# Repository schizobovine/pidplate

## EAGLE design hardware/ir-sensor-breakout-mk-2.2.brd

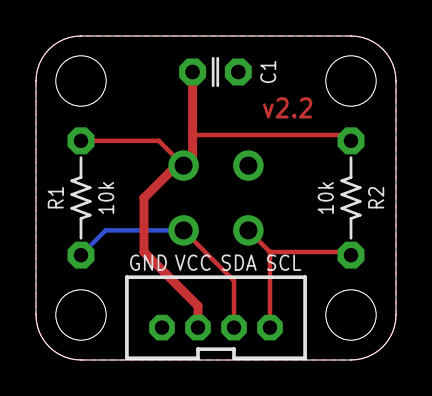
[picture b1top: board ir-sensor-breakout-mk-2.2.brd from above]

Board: 2 copper layers, 20.0 x 18.0 mm, 6 parts (1 on the bottom side), 4 nets.

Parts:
C1: 100nF; C025-024X044
FRAME1: FRAME-LETTERNO_PACKAGE; DUMMY
I2C: M04JST-PTH-VERT; JST-4-PH-VERT-PTH
R1, R2: 10k; RESISTOR-AXIAL-PTH-6.35MM
U1: MLX90614-PTH; TO-39-4

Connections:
GND: C1.2, I2C.1, U1.4
SCL: I2C.4, R2.P$1, U1.1
SDA: I2C.3, R1.P$1, U1.2
VCC: C1.1, I2C.2, R1.P$2, R2.P$2, U1.3

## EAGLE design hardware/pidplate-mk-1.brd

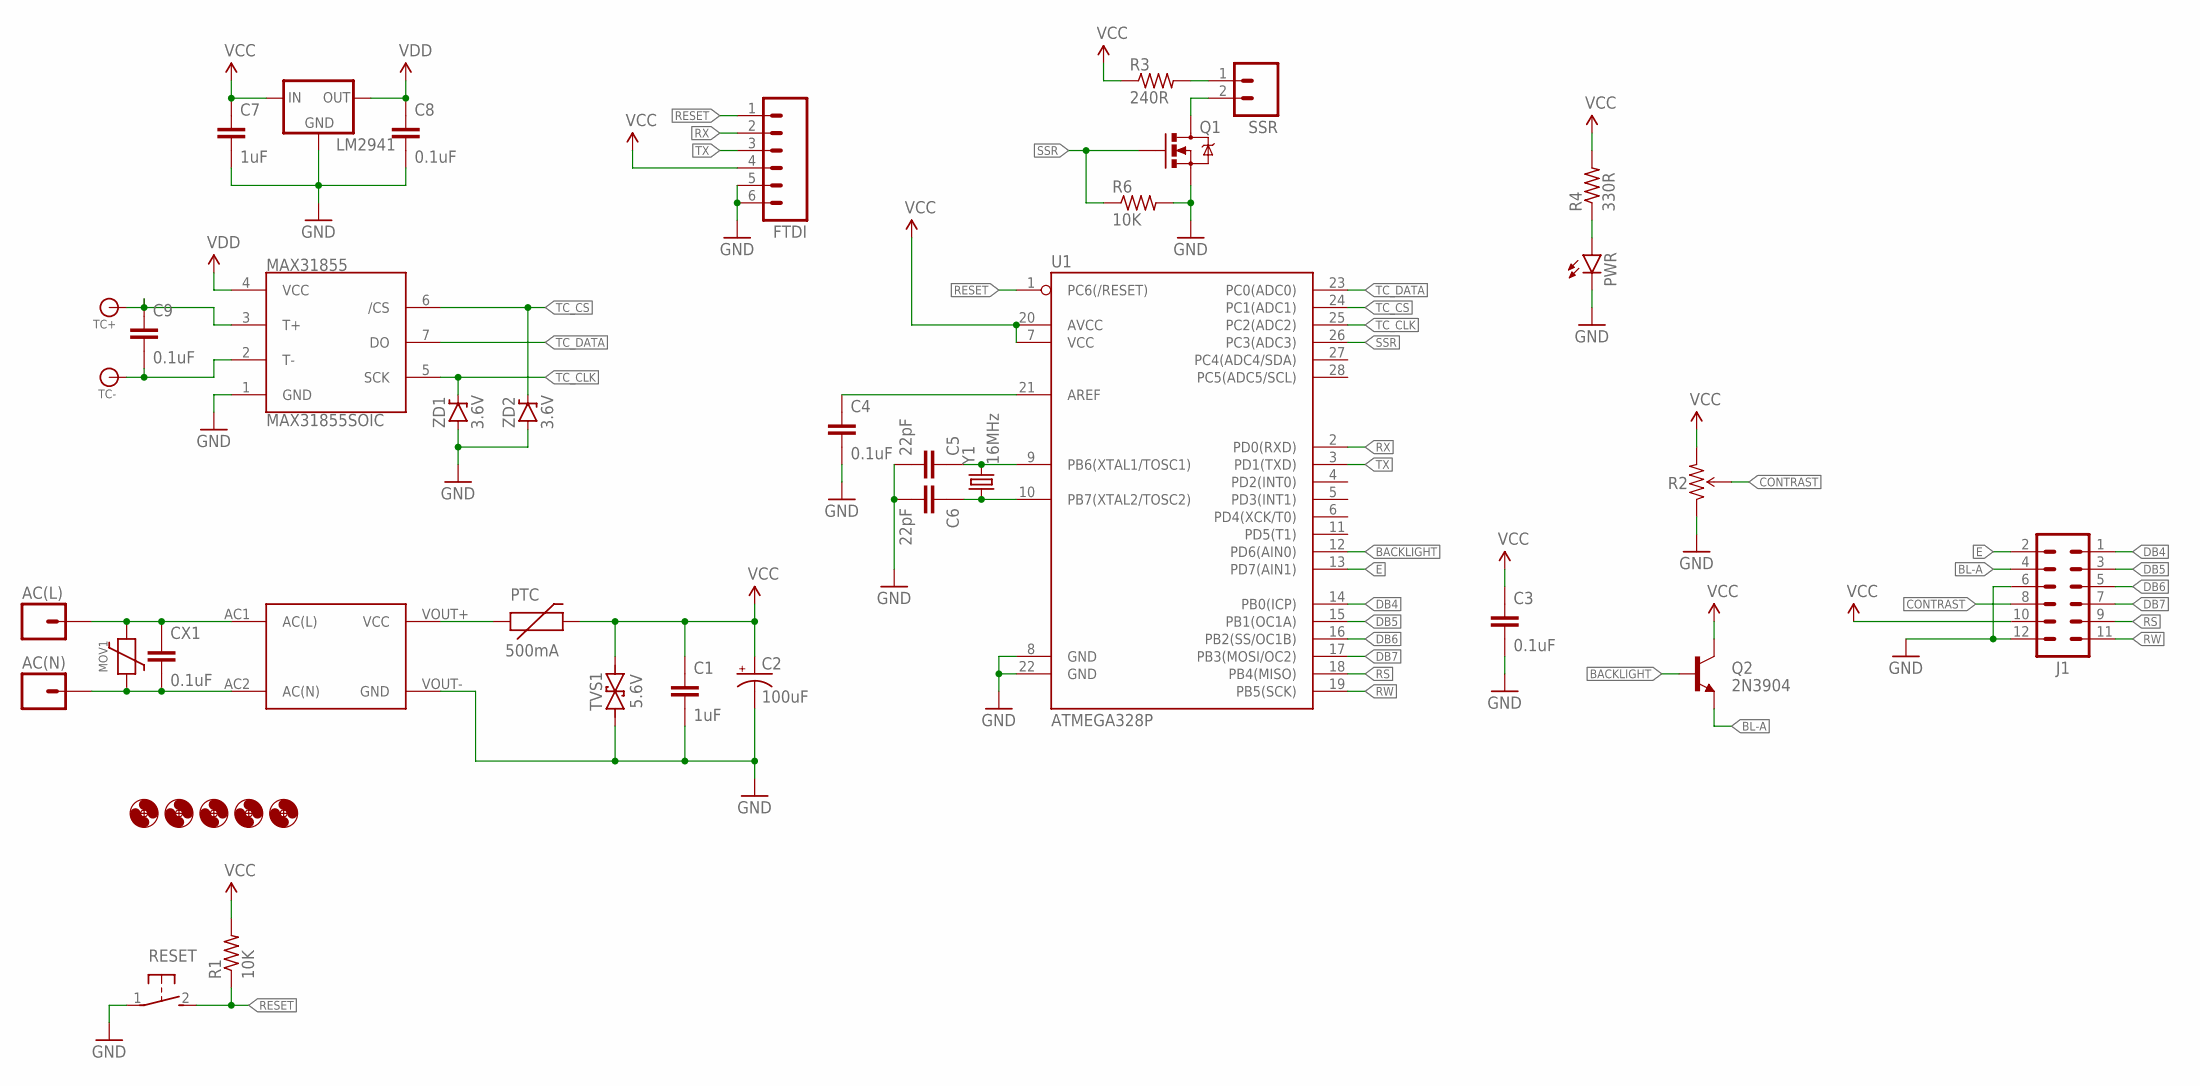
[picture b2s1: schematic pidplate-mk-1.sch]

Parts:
AC(L): M01PTH-1.2MM; 1X01-1.2MM
AC(N): M01PTH-1.2MM; 1X01-1.2MM
C1, C7: 1uF; C025-024X044
C2: 100uF; E2,5-7
C3, C4, C8, C9: 0.1uF; C025-024X044
C5, C6: 22pF; C025-024X044
CX1: 0.1uF; XC10B5
FTDI: M06SIP; 1X06
H1, H2, H3, H4, H5: HOLE#2; HOLE-#2
J1: M06X2PTH; 2X6_PTH
LM2941: L2941; TO-92-AMMO
MAX31855: MAX31855SOIC; SOIC127P600X175-8N
MOV1: VARISITORVAR-5.08MM-PTH; VAR-5.08MM-PTH
PTC: 500mA; PTC
PWR: LED3MM
Q1: 2N7000; TO-92-AMMO
Q2: 2N3904; TO-92-AMMO
R1: 10K; RESISTOR-AXIAL-PTH-5.08MM
R2: 20K; TRIM_POT_PTH
R3: 240R; RESISTOR-AXIAL-PTH-6.35MM
R4: 330R; RESISTOR-AXIAL-PTH-5.08MM
R6: 10K; RESISTOR-AXIAL-PTH-6.35MM
RESET: SPST-NO-TACT3MM-RA; TACTILE-PTH-SIDE
SSR: M02JST-PTH-VERT; JST-2-PH-VERT-PTH
TC+: BANANA_CONNPTH-RA; BANANA-PTH-RA-SAFEWORD
TC-: BANANA_CONNPTH-RA; BANANA-PTH-RA-SAFEWORD
TVS1: 5.6V; DO-41-TVS
U1: ATMEGA328P; DIL28-3
U3: VSK-S1
Y1: 16MHz; HC49U-V
ZD1, ZD2: 3.6V; DIODE-7.68MM

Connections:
BACKLIGHT: Q2.2 (B), U1.12 (PD6(AIN0))
BL-A: J1.4, Q2.3 (E)
CONTRAST: J1.8, R2.2 (WIPER)
DB4: J1.1, U1.14 (PB0(ICP))
DB5: J1.3, U1.15 (PB1(OC1A))
DB6: J1.5, U1.16 (PB2(SS/OC1B))
DB7: J1.7, U1.17 (PB3(MOSI/OC2))
E: J1.2, U1.13 (PD7(AIN1))
GND: C1.2, C2.-, C3.2, C4.2, C5.2, C6.2, C7.2, C8.2, FTDI.5, FTDI.6, J1.6, J1.12, LM2941.2 (GND), MAX31855.1 (GND), PWR.K (C), Q1.1 (S), R2.1 (CCW), R6.P$2 (2), RESET.1, TVS1.P$1 (1), U1.8 (GND), U1.22 (GND), U3.VOUT- (GND), ZD1.A, ZD2.A
unnamed: PTC.P$1 (1), U3.VOUT+ (VCC)
unnamed: C6.1, U1.10 (PB7(XTAL2/TOSC2)), Y1.1
unnamed: C5.1, U1.9 (PB6(XTAL1/TOSC1)), Y1.2
unnamed: C4.1, U1.21 (AREF)
unnamed: R3.P$2 (2), SSR.1
unnamed: C9.2, MAX31855.2 (T-), TC-.P$1, TC-.P$2
unnamed: C9.1, MAX31855.3 (T+), TC+.P$1, TC+.P$2
unnamed: Q1.3 (D), SSR.2
unnamed: PWR.A, R4.P$1 (1)
unnamed: AC(N).P$1, CX1.2, MOV1.1, U3.AC2 (AC(N))
unnamed: AC(L).P$1, CX1.1, MOV1.2, U3.AC1 (AC(L))
RESET: FTDI.1, R1.P$1 (1), RESET.2, U1.1 (PC6(/RESET))
RS: J1.9, U1.18 (PB4(MISO))
RW: J1.11, U1.19 (PB5(SCK))
RX: FTDI.2, U1.2 (PD0(RXD))
SSR: Q1.2 (G), R6.P$1 (1), U1.26 (PC3(ADC3))
TC_CLK: MAX31855.5 (SCK), U1.25 (PC2(ADC2)), ZD1.K (C)
TC_CS: MAX31855.6 (/CS), U1.24 (PC1(ADC1)), ZD2.K (C)
TC_DATA: MAX31855.7 (DO), U1.23 (PC0(ADC0))
TX: FTDI.3, U1.3 (PD1(TXD))
VCC: C1.1, C2.+, C3.1, C7.1, FTDI.4, J1.10, LM2941.1 (IN), PTC.P$2 (2), Q2.1 (C), R1.P$2 (2), R2.3 (CW), R3.P$1 (1), R4.P$2 (2), TVS1.P$2 (2), U1.7 (VCC), U1.20 (AVCC)
VDD: C8.1, LM2941.3 (OUT), MAX31855.4 (VCC)

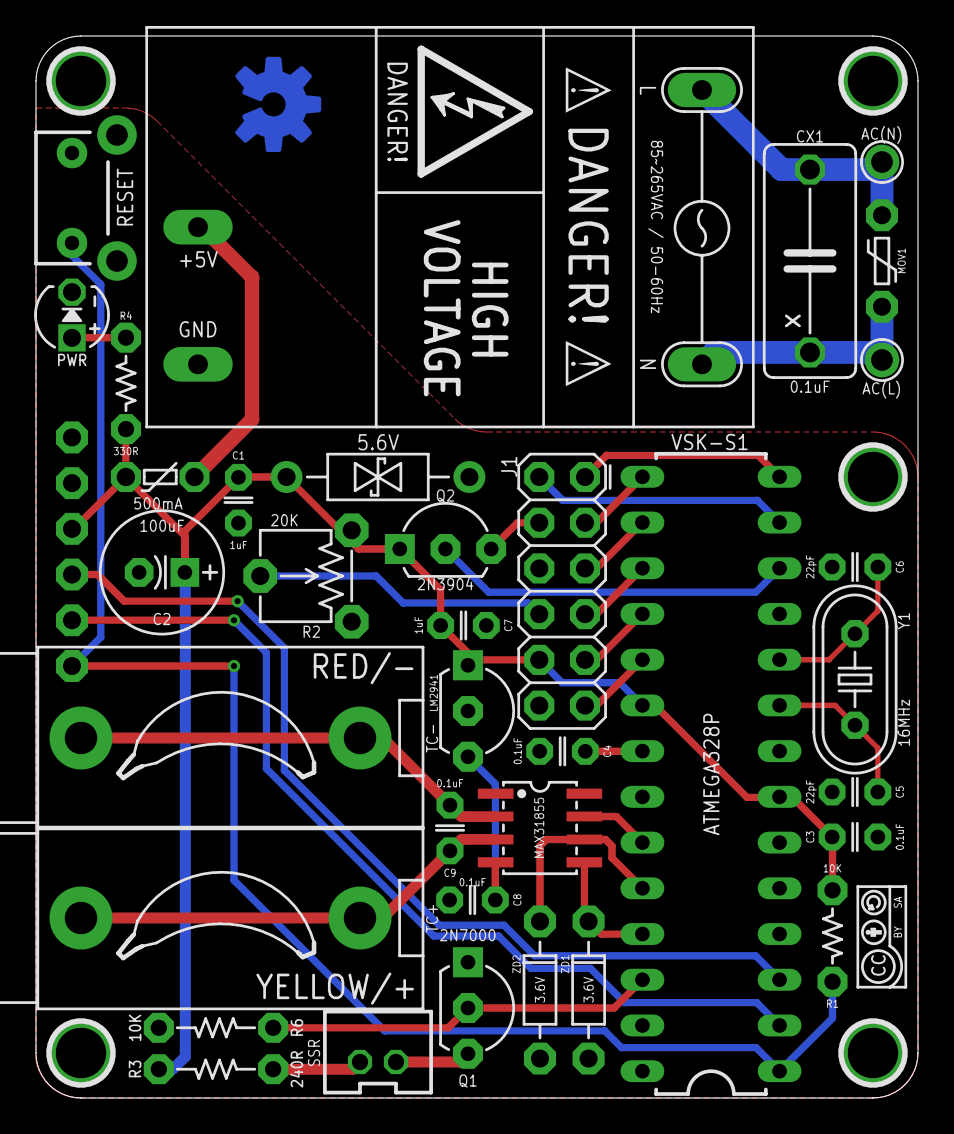
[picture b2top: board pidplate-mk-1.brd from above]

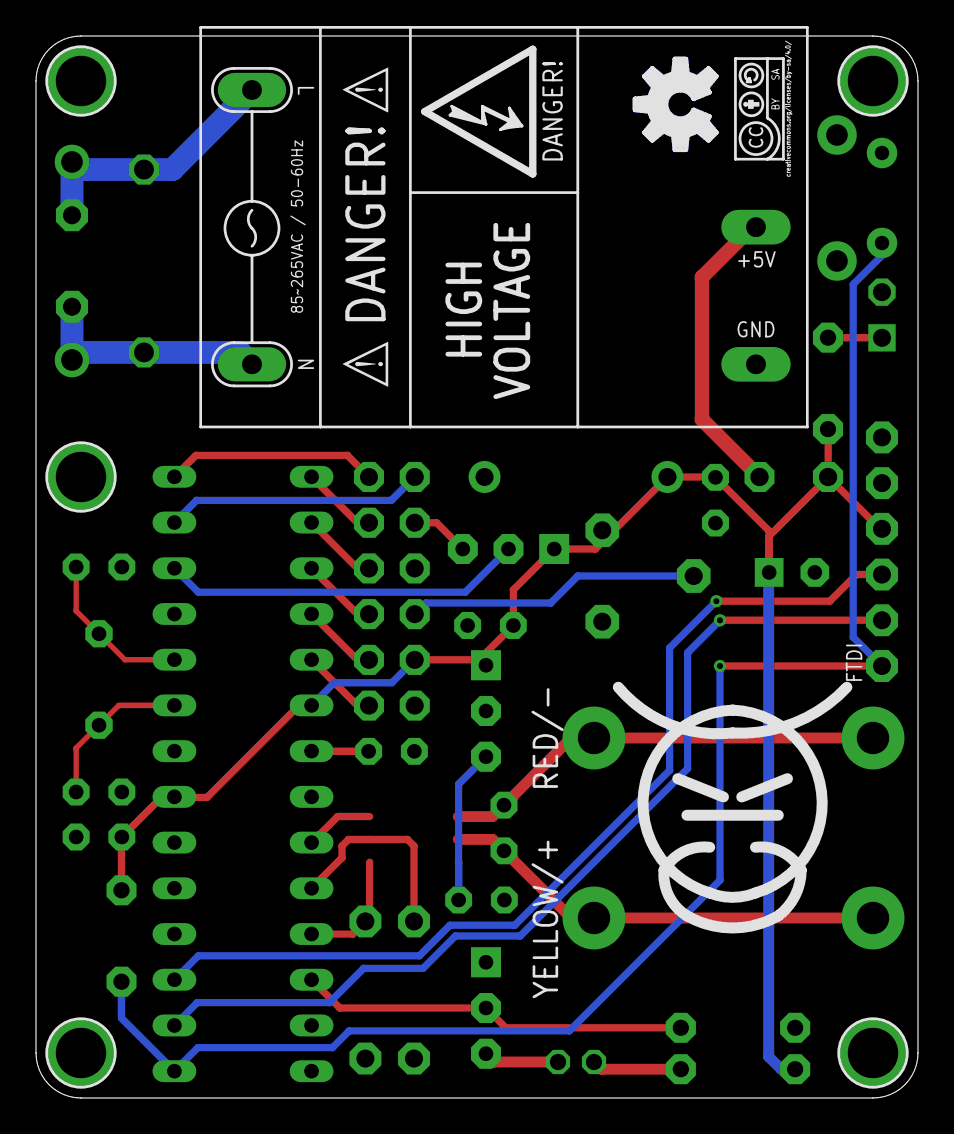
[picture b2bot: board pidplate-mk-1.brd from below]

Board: 2 copper layers, 49.0 x 59.0 mm, 45 parts (3 on the bottom side), 31 nets.

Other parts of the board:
U$1: COW
U$2: CC-BY-SA-4.0-NO-URL
U$3: CC-BY-SA-4.0-URL-BOTTOM
U$4: OSHWLOGO_BOT_0.2

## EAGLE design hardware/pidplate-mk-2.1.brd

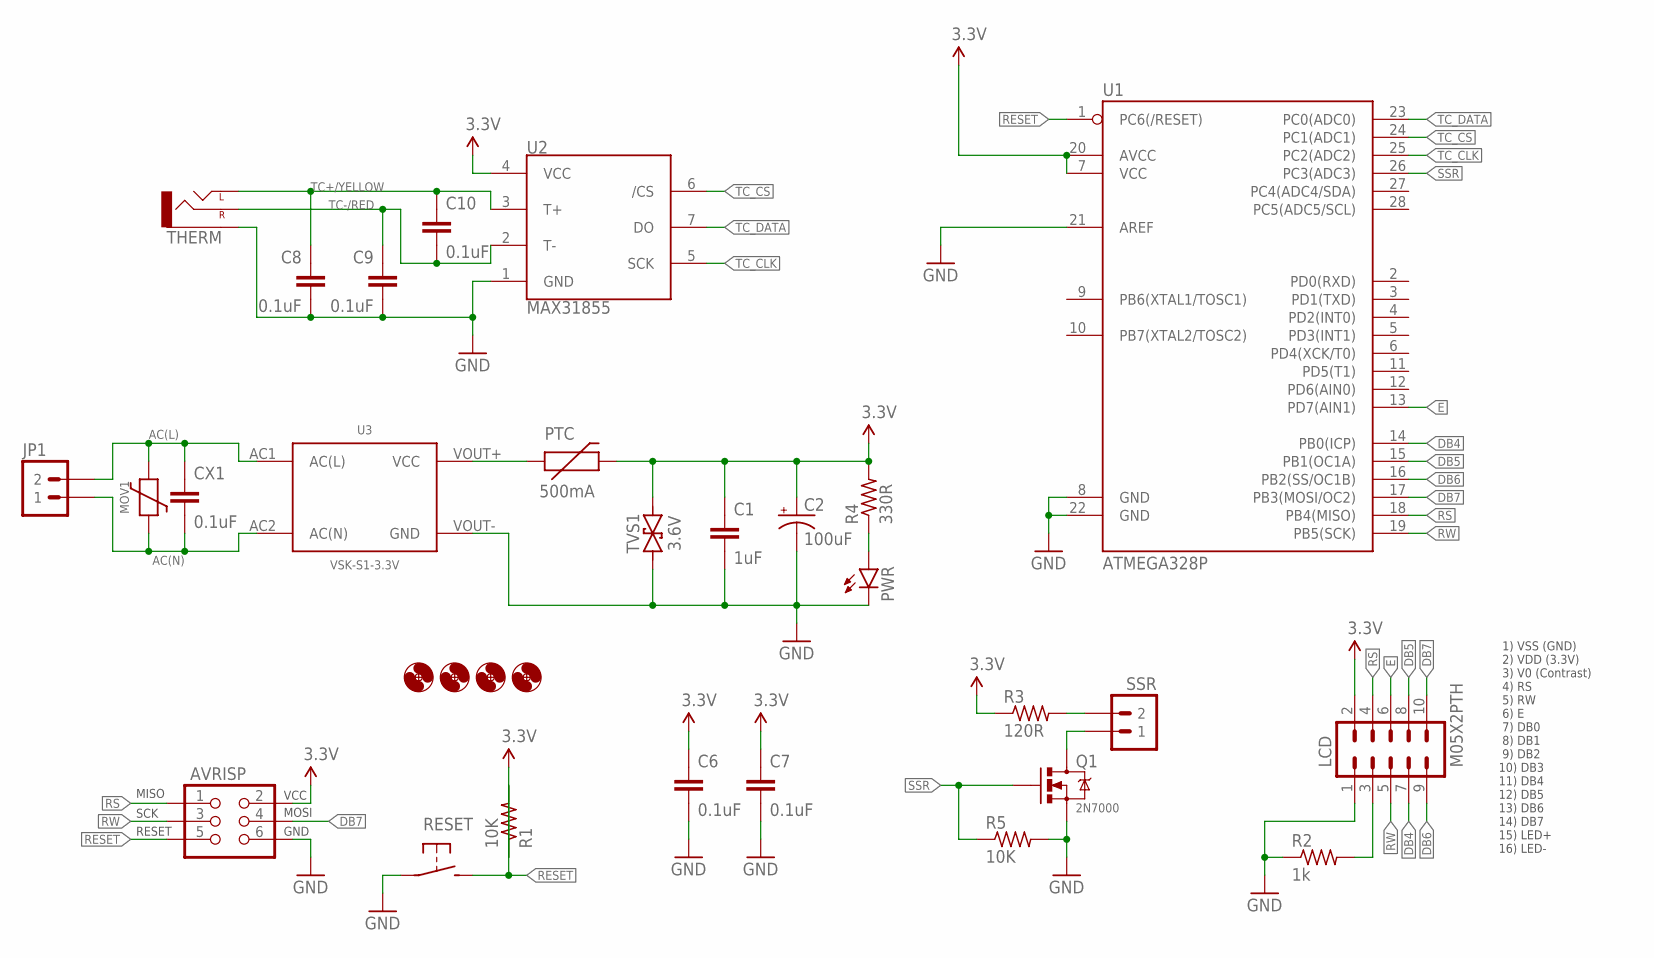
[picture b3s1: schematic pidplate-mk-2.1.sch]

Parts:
AVRISP: AVR_SPI_PRG_6PTH; 2X3
C1: 1uF; C025-024X044
C2: 100uF; E2,5-7
C6, C7, C8, C9, C10: 0.1uF; C025-024X044
CX1: 0.1uF; XC10B5
H1, H2, H3, H4: HOLE#2; HOLE-#2
JP1: M023.5MM; SCREWTERMINAL-3.5MM-2
LCD: M05X2PTH; AVR_ICSP
MOV1: VARISITORVAR-5.08MM-PTH; VAR-5.08MM-PTH
PTC: 500mA; PTC
PWR: LED3MM
Q1: 2N7000; TO-92-AMMO
R1, R5: 10K; RESISTOR-AXIAL-PTH-6.35MM
R2: 1k; RESISTOR-AXIAL-PTH-6.35MM
R3: 120R; RESISTOR-AXIAL-PTH-6.35MM
R4: 330R; RESISTOR-AXIAL-PTH-6.35MM
RESET: SPST-NO-TACT3MM-PTH-SMALL-PADS; DTS-3-SMALL-PADS
SSR: M02JST-PTH-VERT; JST-2-PH-VERT-PTH
THERM: AUDIO-JACK2.5MM; STEREOJACK2.5MM_STEREOJACK2.5MM
TVS1: 3.6V; DO-41-TVS
U1: ATMEGA328P; DIL28-3
U2: MAX31855; SOIC127P600X175-8N
U3: VSK-S1-3.3V; VSK-S1

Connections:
3.3V: AVRISP.2 (VCC), C1.1, C2.+, C6.1, C7.1, LCD.2, PTC.P$2 (2), R1.P$1 (1), R3.P$1 (1), R4.P$2 (2), TVS1.P$2 (2), U1.7 (VCC), U1.20 (AVCC), U2.4 (VCC)
AC(L): CX1.1, JP1.2, MOV1.2, U3.AC1 (AC(L))
AC(N): CX1.2, JP1.1, MOV1.1, U3.AC2 (AC(N))
DB4: LCD.7, U1.14 (PB0(ICP))
DB5: LCD.8, U1.15 (PB1(OC1A))
DB6: LCD.9, U1.16 (PB2(SS/OC1B))
DB7: AVRISP.4 (MOSI), LCD.10, U1.17 (PB3(MOSI/OC2))
E: LCD.6, U1.13 (PD7(AIN1))
GND: AVRISP.6 (GND), C1.2, C2.-, C6.2, C7.2, C8.2, C9.2, LCD.1, PWR.K (C), Q1.1 (S), R2.P$1 (1), R5.P$2 (2), RESET.1, THERM.SHIELD (SLEEVE), TVS1.P$1 (1), U1.8 (GND), U1.21 (AREF), U1.22 (GND), U2.1 (GND), U3.VOUT- (GND)
unnamed: PTC.P$1 (1), U3.VOUT+ (VCC)
unnamed: LCD.3, R2.P$2 (2)
unnamed: R3.P$2 (2), SSR.2
unnamed: Q1.3 (D), SSR.1
unnamed: PWR.A, R4.P$1 (1)
RESET: AVRISP.5 (RESET), R1.P$2 (2), RESET.2, U1.1 (PC6(/RESET))
RS: AVRISP.1 (MISO), LCD.4, U1.18 (PB4(MISO))
RW: AVRISP.3 (SCK), LCD.5, U1.19 (PB5(SCK))
SSR: Q1.2 (G), R5.P$1 (1), U1.26 (PC3(ADC3))
TC+/YELLOW: C8.1, C10.1, THERM.RING1 (LEFT), THERM.RING2 (LEFT), U2.3 (T+)
TC-/RED: C9.1, C10.2, THERM.TIP (RIGHT), U2.2 (T-)
TC_CLK: U1.25 (PC2(ADC2)), U2.5 (SCK)
TC_CS: U1.24 (PC1(ADC1)), U2.6 (/CS)
TC_DATA: U1.23 (PC0(ADC0)), U2.7 (DO)

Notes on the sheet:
1) VSS (GND) 2) VDD (3.3V) 3) V0 (Contrast) 4) RS 5) RW 6) E 7) DB0 8) DB1 9) DB2 10) DB3 11) DB4 12) DB5 13) DB6 14) DB7 15) LED+ 16) LED-

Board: 2 copper layers, 35 parts (2 on the bottom side), 23 nets, no tracks yet.

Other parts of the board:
U$1, U$4: OSHWLOGO_BOT_0.2
U$2, U$3: CC-BY-SA-4.0-NO-URL

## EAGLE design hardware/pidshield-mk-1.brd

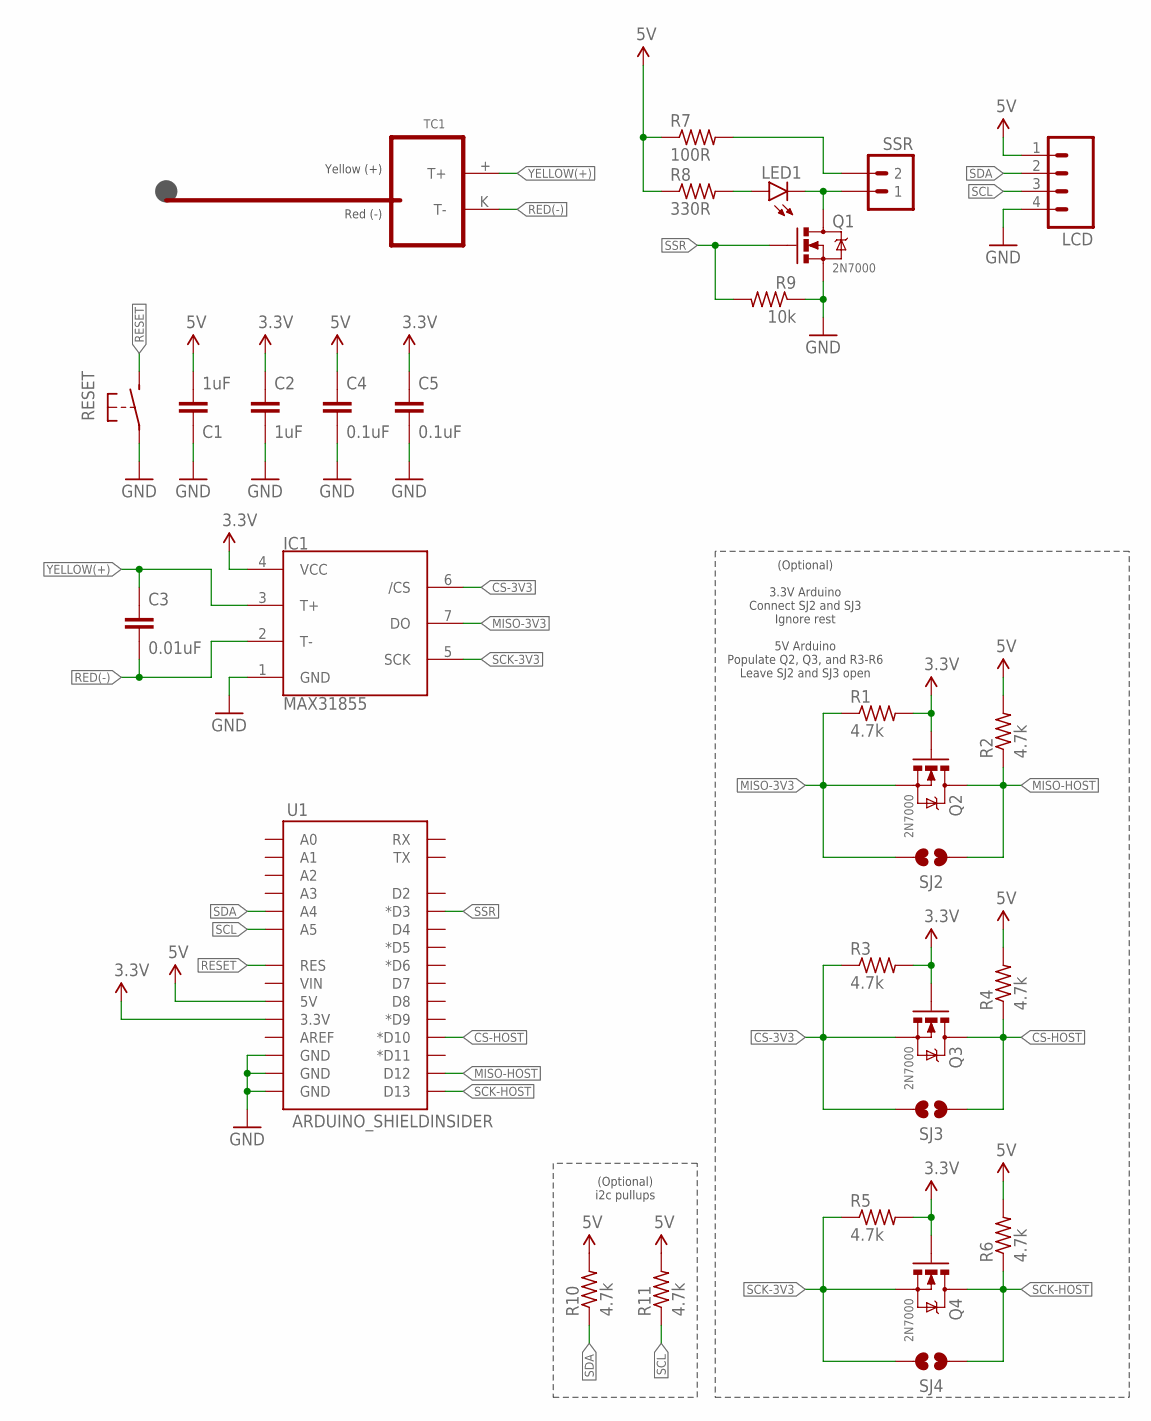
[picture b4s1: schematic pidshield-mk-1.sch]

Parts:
C1, C2: 1uF; C025-024X044
C3: 0.01uF; C025-024X044
C4, C5: 0.1uF; C025-024X044
IC1: MAX31855; SOIC127P600X175-8N
LCD: M04JST_XH_RA; JST-4-XH-RA-PTH
LED1: LED3MM
Q1, Q2, Q3, Q4: 2N7000; TO-92-AMMO
R1, R2, R3, R4, R5, R6, R10, R11: 4.7k; RESISTOR-AXIAL-PTH-6.35MM
R7: 100R; RESISTOR-AXIAL-PTH-6.35MM
R8: 330R; RESISTOR-AXIAL-PTH-6.35MM
R9: 10k; RESISTOR-AXIAL-PTH-6.35MM
RESET: SPST-NO-TACT3MM-RA; TACTILE-PTH-SIDE
SJ2, SJ3, SJ4: JUMPER-PAD-2-NOYES_SILK; PAD-JUMPER-2-NO_YES_SILK
SSR: M02JST-PTH-RA-SMALLPADS; JST-2-PH-RA-PTH-SMALLPADS
TC1: PCC-SMP-K; PCC-SMP
U1: ARDUINO_SHIELDINSIDER; ARDUINO_SHIELD_NOOUTLINE_INSIDE

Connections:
3.3V: C2.1, C5.1, IC1.4 (VCC), Q2.2 (G), Q3.2 (G), Q4.2 (G), R1.P$2 (2), R3.P$2 (2), R5.P$2 (2), U1.3.3V
5V: C1.2, C4.1, LCD.1, R2.P$2 (2), R4.P$2 (2), R6.P$2 (2), R7.P$1 (1), R8.P$1 (1), R10.P$2 (2), R11.P$2 (2), U1.5V
CS-3V3: IC1.6 (/CS), Q3.1 (S), R3.P$1 (1), SJ3.2
CS-HOST: Q3.3 (D), R4.P$1 (1), SJ3.1, U1.D10 (*D10)
GND: C1.1, C2.2, C4.2, C5.2, IC1.1 (GND), LCD.4, Q1.1 (S), R9.P$1 (1), RESET.1, U1.GND@0 (GND), U1.GND@1 (GND), U1.GND@2 (GND)
MISO-3V3: IC1.7 (DO), Q2.1 (S), R1.P$1 (1), SJ2.2
MISO-HOST: Q2.3 (D), R2.P$1 (1), SJ2.1, U1.D12
unnamed: LED1.A, R8.P$2 (2)
unnamed: LED1.K (C), Q1.3 (D), SSR.1
unnamed: R7.P$2 (2), SSR.2
RED(-): C3.2, IC1.2 (T-), TC1.K (T-)
RESET: RESET.2, U1.RES
SCK-3V3: IC1.5 (SCK), Q4.1 (S), R5.P$1 (1), SJ4.2
SCK-HOST: Q4.3 (D), R6.P$1 (1), SJ4.1, U1.D13
SCL: LCD.3, R11.P$1 (1), U1.A5
SDA: LCD.2, R10.P$1 (1), U1.A4
SSR: Q1.2 (G), R9.P$2 (2), U1.D3 (*D3)
YELLOW(+): C3.1, IC1.3 (T+), TC1.+ (T+)

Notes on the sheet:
(Optional) 3.3V Arduino Connect SJ2 and SJ3 Ignore rest 5V Arduino Populate Q2, Q3, and R3-R6 Leave SJ2 and SJ3 open
(Optional) i2c pullups

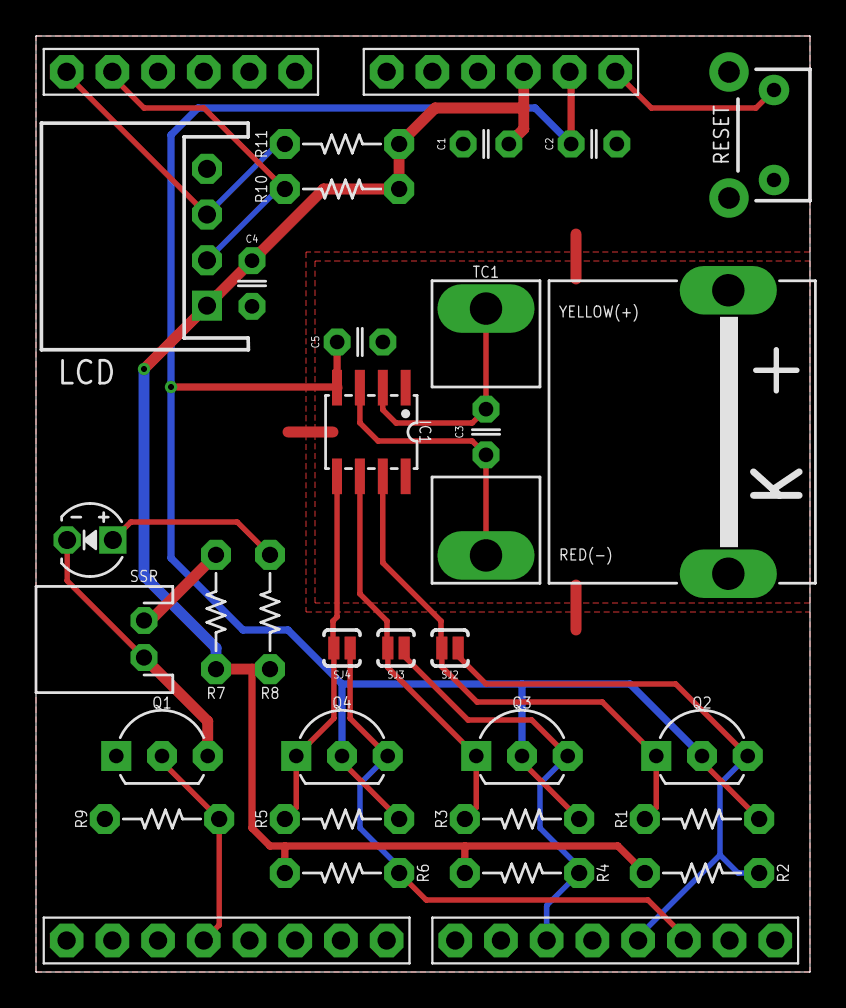
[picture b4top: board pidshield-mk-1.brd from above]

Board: 2 copper layers, 43.0 x 52.0 mm, 30 parts (0 on the bottom side), 18 nets.

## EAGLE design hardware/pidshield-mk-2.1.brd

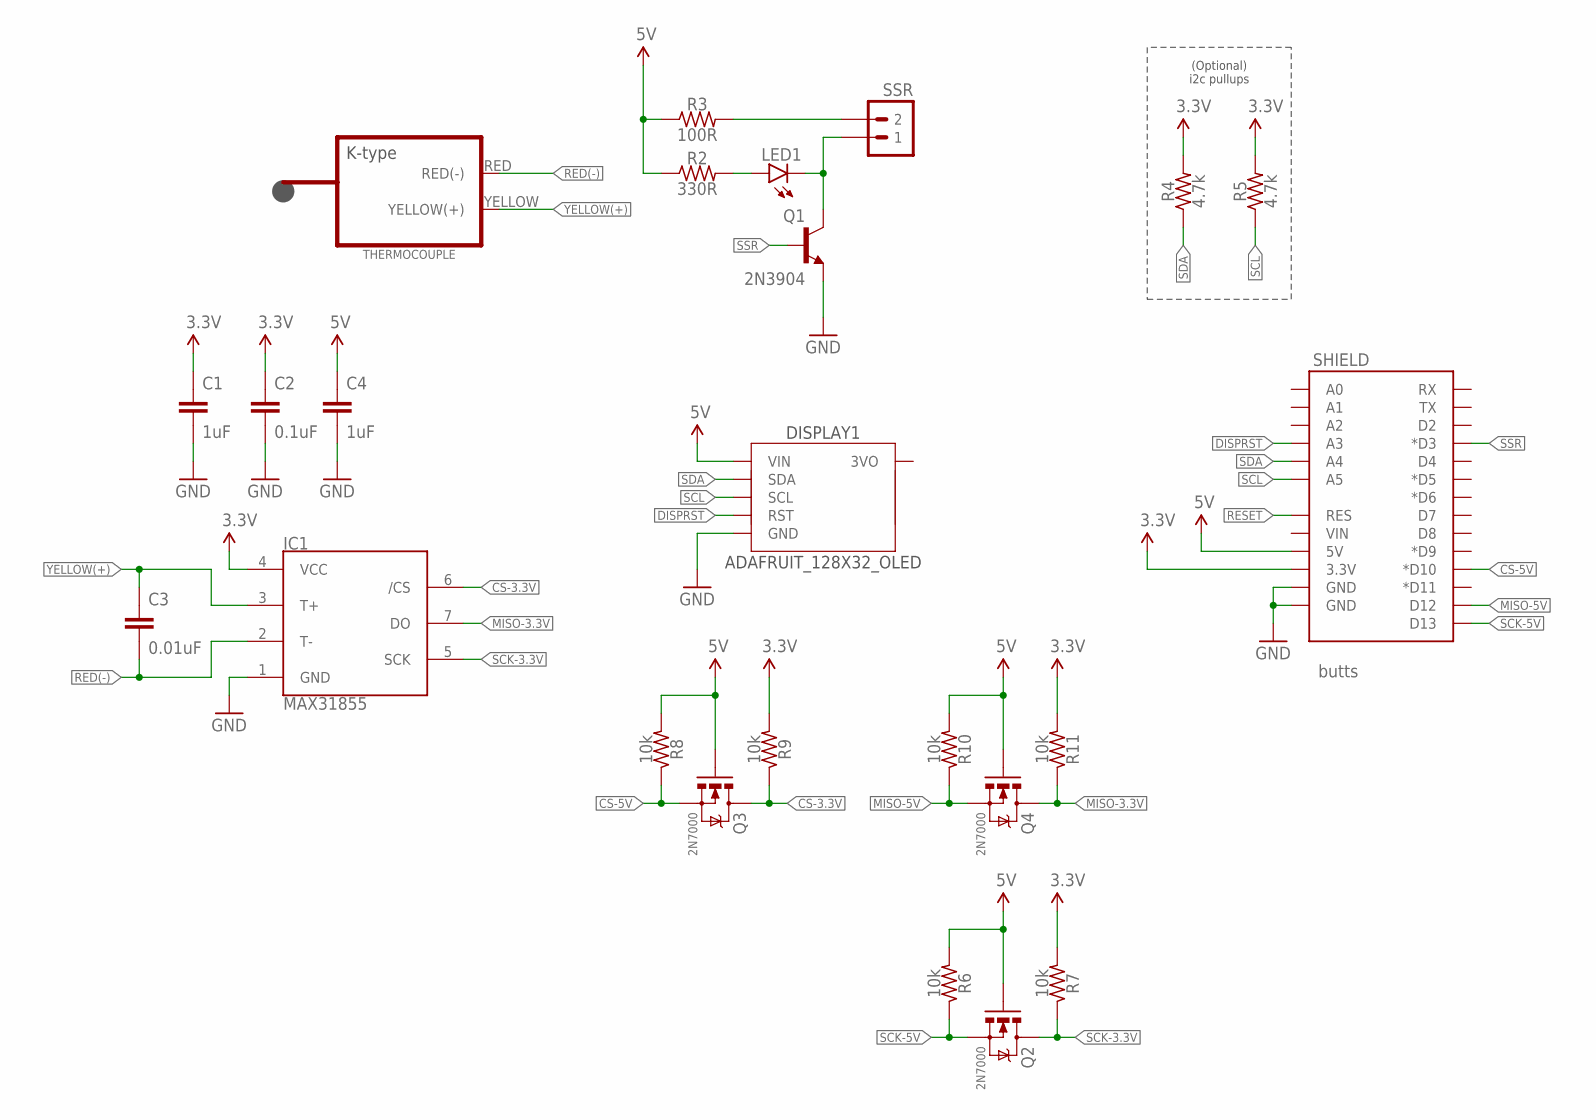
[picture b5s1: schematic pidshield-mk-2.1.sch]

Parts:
C1, C4: 1uF; C025-024X044
C2: 0.1uF; C025-024X044
C3: 0.01uF; C0805
DISPLAY1: ADAFRUIT_128X32_OLED; ADAFRUIT_128X32_OLED_I2C_CLOSER_NS
IC1: MAX31855; SOIC127P600X175-8N
LED1: LED3MM-LESS; LED3MM-LESSSILK
Q1: 2N3904; TO-92-AMMO
Q2, Q3, Q4: 2N7000; TO-92-AMMO
R2: 330R; RESISTOR-AXIAL-PTH-5.08MM
R3: 100R; RESISTOR-AXIAL-PTH-5.08MM
R4, R5: 4.7k; RESISTOR-AXIAL-PTH-5.08MM
R6, R7, R8, R9, R10, R11: 10k; RESISTOR-AXIAL-PTH-5.08MM
SHIELD: butts; ARDUINO_SHIELD_NOOUTLINE_INSIDE_SMALLER
SSR: M02JST-PTH-RA-SMALLPADS; JST-2-PH-RA-PTH-SMALLPADS
THERMOCOUPLE: THERMOCOUPLE-CONNECTORMINI-PCB; PCC-SMP

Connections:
3.3V: C1.1, C2.1, IC1.4 (VCC), R4.P$2 (2), R5.P$2 (2), R7.P$2 (2), R9.P$2 (2), R11.P$2 (2), SHIELD.3.3V
5V: C4.1, DISPLAY1.VIN, Q2.2 (G), Q3.2 (G), Q4.2 (G), R2.P$1 (1), R3.P$1 (1), R6.P$2 (2), R8.P$2 (2), R10.P$2 (2), SHIELD.5V
CS-3.3V: IC1.6 (/CS), Q3.3 (D), R9.P$1 (1)
CS-5V: Q3.1 (S), R8.P$1 (1), SHIELD.D10 (*D10)
DISPRST: DISPLAY1.RST, SHIELD.A3
GND: C1.2, C2.2, C4.2, DISPLAY1.GND, IC1.1 (GND), Q1.1 (E), SHIELD.GND@0 (GND), SHIELD.GND@1 (GND)
MISO-3.3V: IC1.7 (DO), Q4.3 (D), R11.P$1 (1)
MISO-5V: Q4.1 (S), R10.P$1 (1), SHIELD.D12
unnamed: LED1.A, R2.P$2 (2)
unnamed: LED1.K (C), Q1.3 (C), SSR.1
unnamed: R3.P$2 (2), SSR.2
RED(-): C3.2, IC1.2 (T-), THERMOCOUPLE.RED (RED(-))
RESET: SHIELD.RES
SCK-3.3V: IC1.5 (SCK), Q2.3 (D), R7.P$1 (1)
SCK-5V: Q2.1 (S), R6.P$1 (1), SHIELD.D13
SCL: DISPLAY1.SCL, R5.P$1 (1), SHIELD.A5
SDA: DISPLAY1.SDA, R4.P$1 (1), SHIELD.A4
SSR: Q1.2 (B), SHIELD.D3 (*D3)
YELLOW(+): C3.1, IC1.3 (T+), THERMOCOUPLE.YELLOW (YELLOW(+))

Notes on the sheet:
(Optional) i2c pullups

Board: 2 copper layers, 30 parts (2 on the bottom side), 18 nets, no tracks yet.

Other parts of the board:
U$2: COW
U$3: COW_SMALL
U$4, U$5: CC-BY-SA-4.0-NO-URL
U$6: OSHWLOGO_TOP_0.2_A
U$7: OSHWLOGO_BOT_0.2_A

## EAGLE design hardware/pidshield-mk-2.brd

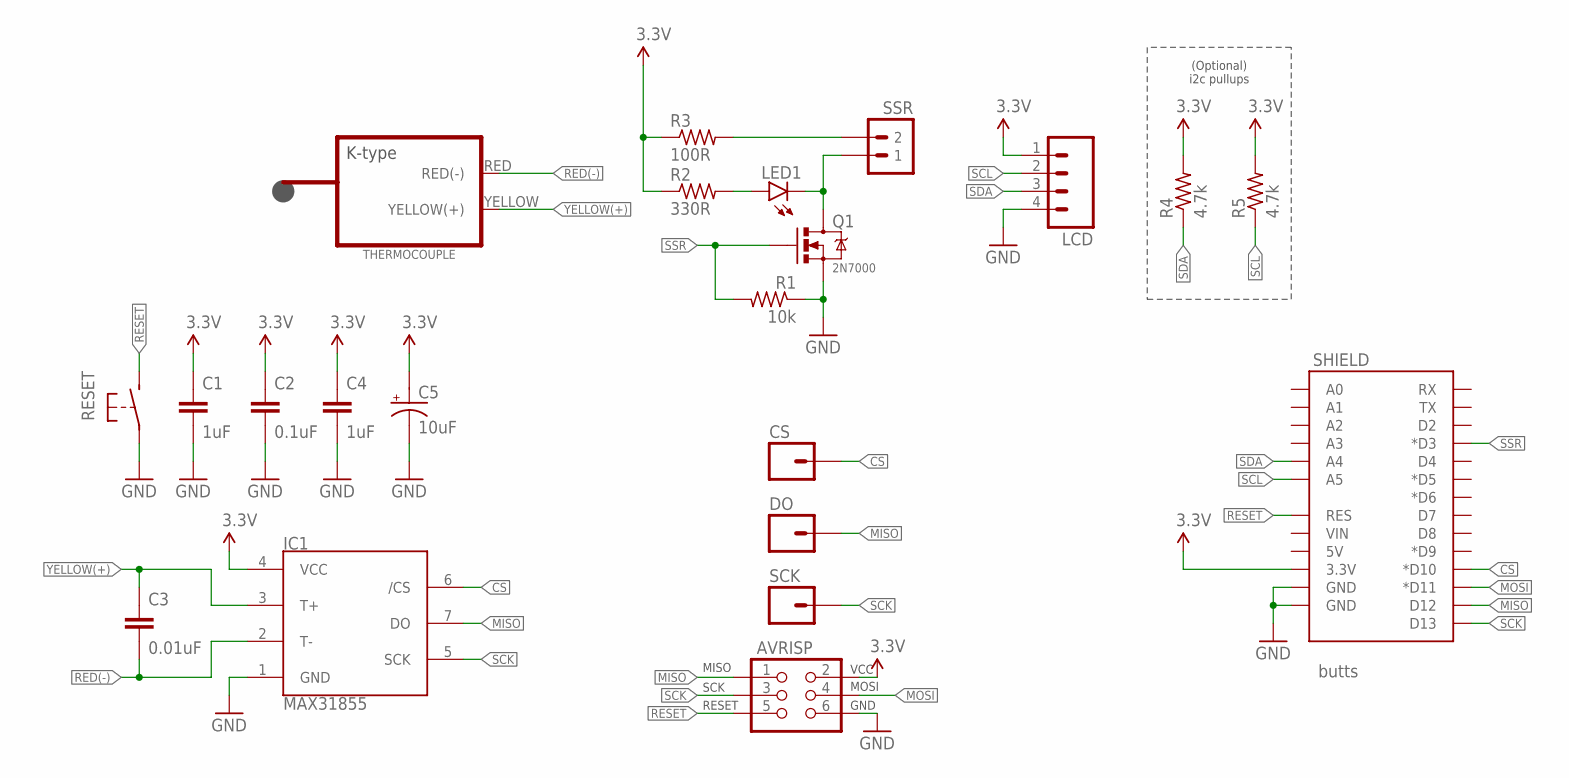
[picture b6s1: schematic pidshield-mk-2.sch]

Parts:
AVRISP: AVR_SPI_PRG_6PTH; 2X3
C1, C4: 1uF; C025-024X044
C2: 0.1uF; C025-024X044
C3: 0.01uF; C025-024X044
C5: 10uF; E2-5
CS: M01PTH; 1X01
DO: M01PTH; 1X01
IC1: MAX31855; SOIC127P600X175-8N
LCD: M04JST_XH_RA; JST-4-XH-RA-PTH
LED1: LED3MM
Q1: 2N7000; TO-92-AMMO
R1: 10k; RESISTOR-AXIAL-PTH-6.35MM
R2: 330R; RESISTOR-AXIAL-PTH-6.35MM
R3: 100R; RESISTOR-AXIAL-PTH-6.35MM
R4, R5: 4.7k; RESISTOR-AXIAL-PTH-6.35MM
RESET: SPST-NO-TACT6MM-PTH-SMALL-PADS; DTS-6-SMALL-PADS
SCK: M01PTH; 1X01
SHIELD: butts; ARDUINO_SHIELD_NOOUTLINE_INSIDE_SMALLER
SSR: M02JST-PTH-RA-SMALLPADS; JST-2-PH-RA-PTH-SMALLPADS
THERMOCOUPLE: THERMOCOUPLE-CONNECTORMINI-PCB; PCC-SMP

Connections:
3.3V: AVRISP.2 (VCC), C1.1, C2.1, C4.1, C5.+, IC1.4 (VCC), LCD.1, R2.P$1 (1), R3.P$1 (1), R4.P$2 (2), R5.P$2 (2), SHIELD.3.3V
CS: CS.1, IC1.6 (/CS), SHIELD.D10 (*D10)
GND: AVRISP.6 (GND), C1.2, C2.2, C4.2, C5.-, IC1.1 (GND), LCD.4, Q1.1 (S), R1.P$1 (1), RESET.1, RESET.2 (1), SHIELD.GND@0 (GND), SHIELD.GND@1 (GND)
MISO: AVRISP.1 (MISO), DO.1, IC1.7 (DO), SHIELD.D12
MOSI: AVRISP.4 (MOSI), SHIELD.D11 (*D11)
unnamed: LED1.A, R2.P$2 (2)
unnamed: LED1.K (C), Q1.3 (D), SSR.1
unnamed: R3.P$2 (2), SSR.2
RED(-): C3.2, IC1.2 (T-), THERMOCOUPLE.RED (RED(-))
RESET: AVRISP.5 (RESET), RESET.3 (2), RESET.4 (2), SHIELD.RES
SCK: AVRISP.3 (SCK), IC1.5 (SCK), SCK.1, SHIELD.D13
SCL: LCD.2, R5.P$1 (1), SHIELD.A5
SDA: LCD.3, R4.P$1 (1), SHIELD.A4
SSR: Q1.2 (G), R1.P$2 (2), SHIELD.D3 (*D3)
YELLOW(+): C3.1, IC1.3 (T+), THERMOCOUPLE.YELLOW (YELLOW(+))

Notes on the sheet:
(Optional) i2c pullups

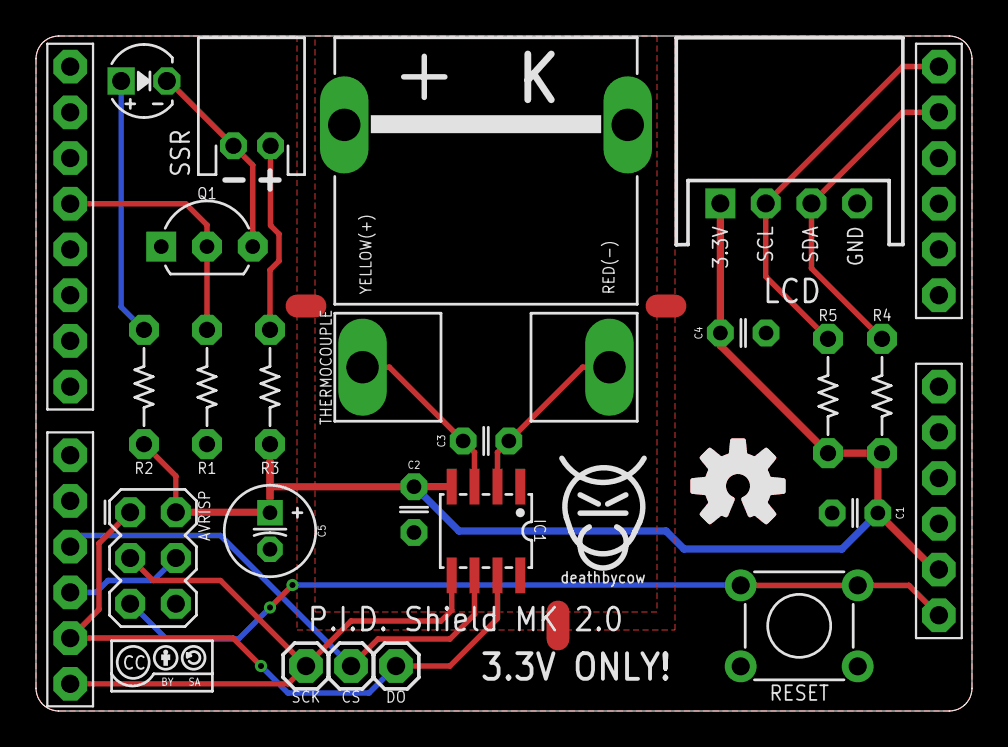
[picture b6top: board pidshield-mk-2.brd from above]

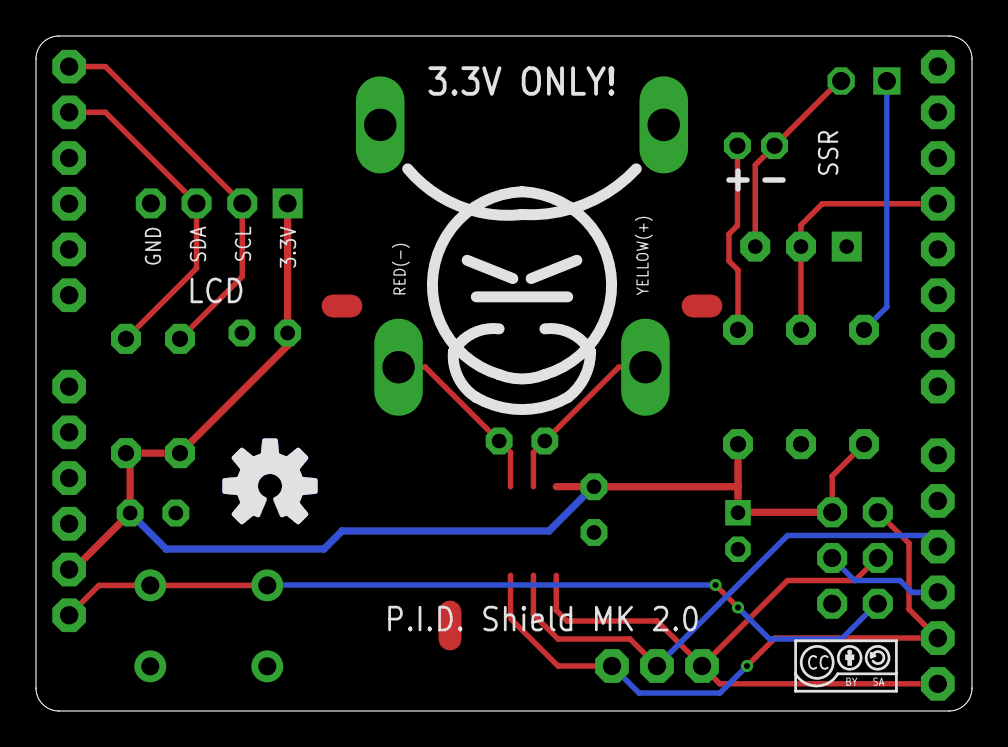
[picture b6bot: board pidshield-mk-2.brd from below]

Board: 2 copper layers, 52.0 x 37.5 mm, 28 parts (2 on the bottom side), 15 nets.

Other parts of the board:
U$2: COW
U$3: COW_SMALL
U$4, U$5: CC-BY-SA-4.0-NO-URL
U$6: OSHWLOGO_TOP_0.2_A
U$7: OSHWLOGO_BOT_0.2_A

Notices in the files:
parts and their libraries:
A_butts: creativecommons.org/licenses/by-sa/4.0
